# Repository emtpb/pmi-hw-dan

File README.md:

# PMI-DAN (Diodes And NMOS)

This pcb is designed for the course PMI (Practical course Microcontroller and Interface electronics). It features four LEDs and four open-drain NMOSFETs. It can be chained with [PMI-CARLOS](https://github.com/emtpb/pmi-hw-carlos) (thus only four of the available eight GPIO pins are used).

Pin header and sockets are compatible with
[Digilents Pmod](https://digilent.com/reference/pmod/start) interface.

The board can be used with [PMI-BOB2](https://github.com/emtpb/pmi-hw-bob2)
pcb.

# Interactive BOM

An interactive html BOM page with pcb layout and material placement can be found [here](https://emtpb.github.io/pmi-hw-dan/bom/ibom.html).

# Changelog

## 1.0
* First prototype

## 1.1
* First release

## 1.2
* Convert project to Kicad 6
* Round pcb corners
* Place output labeling above pin header

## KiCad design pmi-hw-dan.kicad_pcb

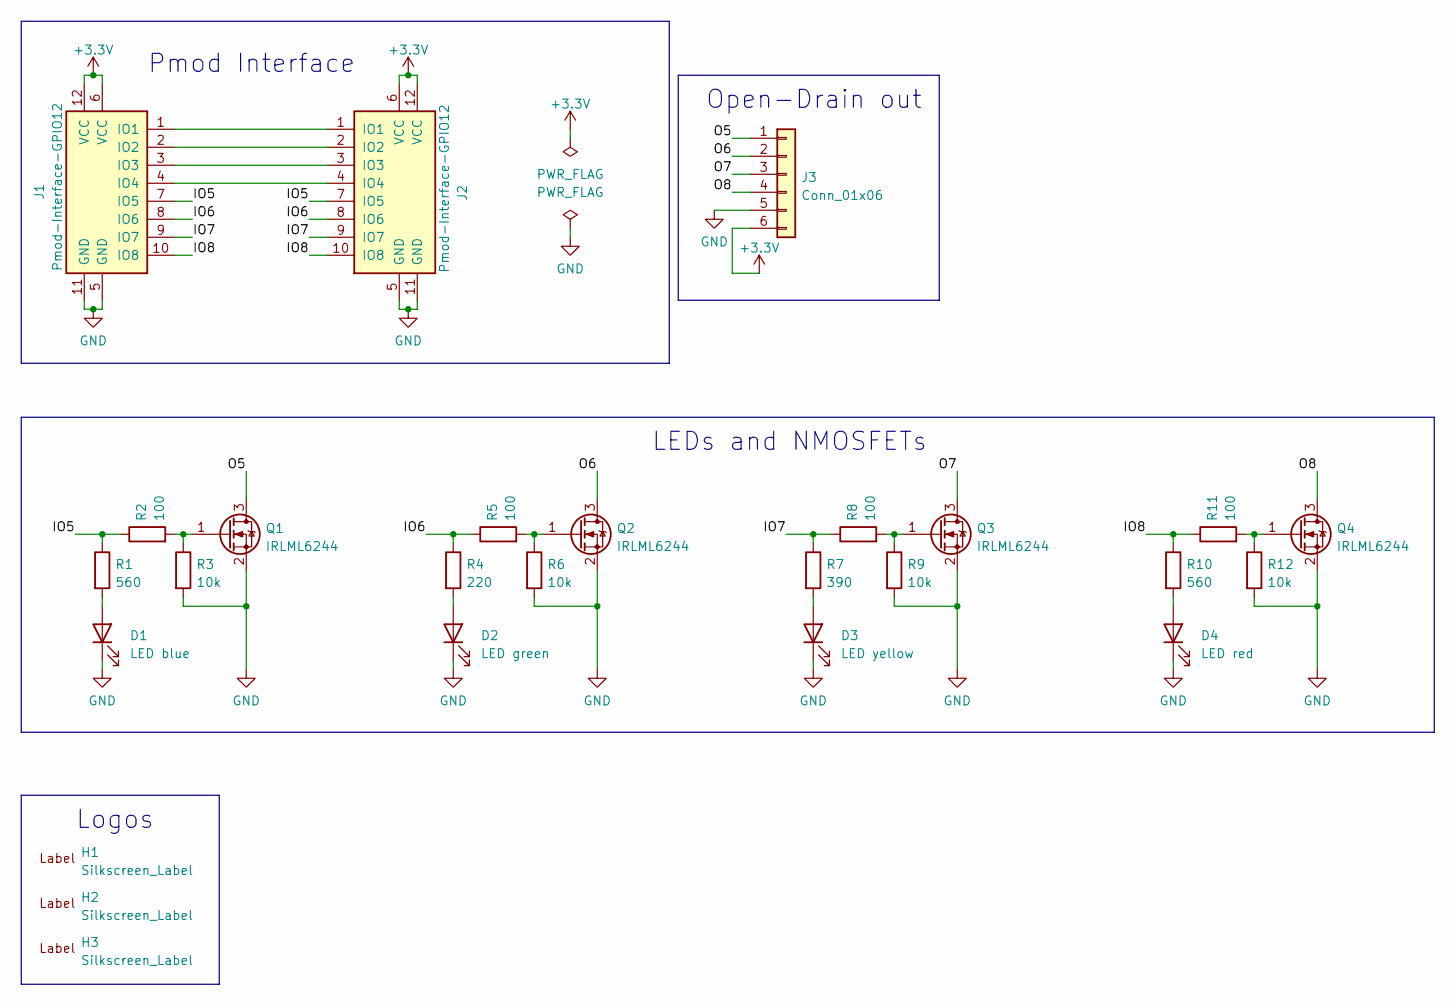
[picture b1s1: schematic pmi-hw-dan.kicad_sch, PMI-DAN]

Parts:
D1: LED blue; LED_0603_1608Metric; Manufacturer Part No LB Q39G-L2OO-35-1; Mouser Part No 720-LBQ39GL2N2351
D2: LED green; LED_0603_1608Metric; Manufacturer Part No LG Q396-PS-35; Digikey Part No 475-3754-1-ND
D3: LED yellow; LED_0603_1608Metric; Manufacturer Part No LY Q396-P1Q2-36; Digikey Part No 475-3467-1-ND
D4: LED red; LED_0603_1608Metric; Manufacturer Part No LS Q976-NR-1-0-20-R18; Digikey Part No 475-2512-1-ND
H1: Silkscreen_Label; UPB-Logo_En_12.3X4.3mm
H2, H3: Silkscreen_Label; EMT-Logo_8.2x4.1mm_Silkscreen
J1: Pmod-Interface-GPIO12; Pmod_Interface_Male12
J2: Pmod-Interface-GPIO12; Pmod_Interface_Female12
J3: Conn_01x06; PinHeader_1x06_P2.54mm_Vertical
Q1, Q2, Q3: IRLML6244; SOT-23
Q4: IRLML6244; SOT-23; Manufacturer Part No IRLML6244TRPBF; Digikey Part No IRLML6244TRPBFCT-ND
R1, R10: 560; R_0603_1608Metric
R2, R5, R8, R11: 100; R_0603_1608Metric
R3, R6, R9, R12: 10k; R_0603_1608Metric
R4: 220; R_0603_1608Metric
R7: 390; R_0603_1608Metric

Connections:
+3.3V: J1.6 (VCC), J1.12 (VCC), J2.6 (VCC), J2.12 (VCC), J3.6
/IO5: J1.7 (IO5), J2.7 (IO5), R1.1, R2.1
/IO6: J1.8 (IO6), J2.8 (IO6), R4.1, R5.1
/IO7: J1.9 (IO7), J2.9 (IO7), R7.1, R8.1
/IO8: J1.10 (IO8), J2.10 (IO8), R10.1, R11.1
/O5: J3.1, Q1.3 (D)
/O6: J3.2, Q2.3 (D)
/O7: J3.3, Q3.3 (D)
/O8: J3.4, Q4.3 (D)
GND: D1.1 (K), D2.1 (K), D3.1 (K), D4.1 (K), J1.5 (GND), J1.11 (GND), J2.5 (GND), J2.11 (GND), J3.5, Q1.2 (S), Q2.2 (S), Q3.2 (S), Q4.2 (S), R3.2, R6.2, R9.2, R12.2
unnamed: D1.2 (A), R1.2
unnamed: D2.2 (A), R4.2
unnamed: D3.2 (A), R7.2
unnamed: D4.2 (A), R10.2
unnamed: J1.1 (IO1), J2.1 (IO1)
unnamed: J1.2 (IO2), J2.2 (IO2)
unnamed: J1.3 (IO3), J2.3 (IO3)
unnamed: J1.4 (IO4), J2.4 (IO4)
unnamed: Q1.1 (G), R2.2, R3.1
unnamed: Q2.1 (G), R5.2, R6.1
unnamed: Q3.1 (G), R8.2, R9.1
unnamed: Q4.1 (G), R11.2, R12.1

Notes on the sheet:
Open-Drain out
Pmod Interface
LEDs and NMOSFETs
Logos

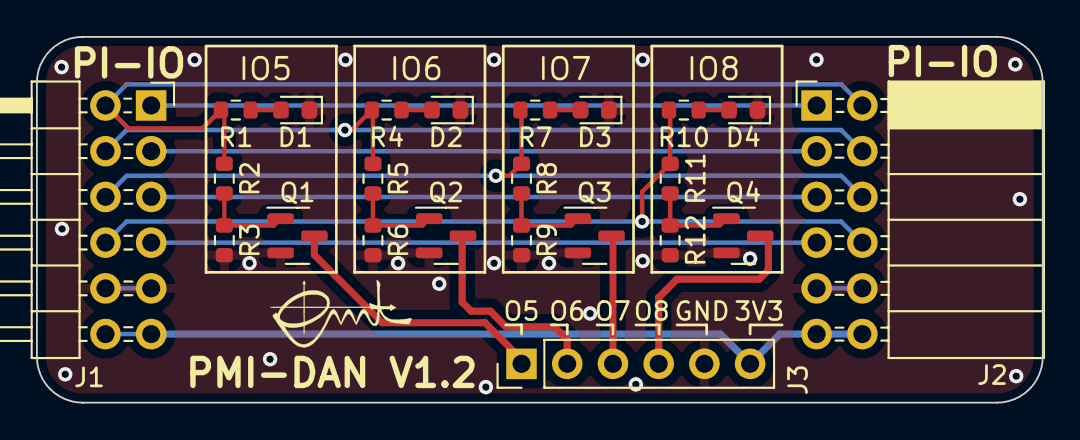
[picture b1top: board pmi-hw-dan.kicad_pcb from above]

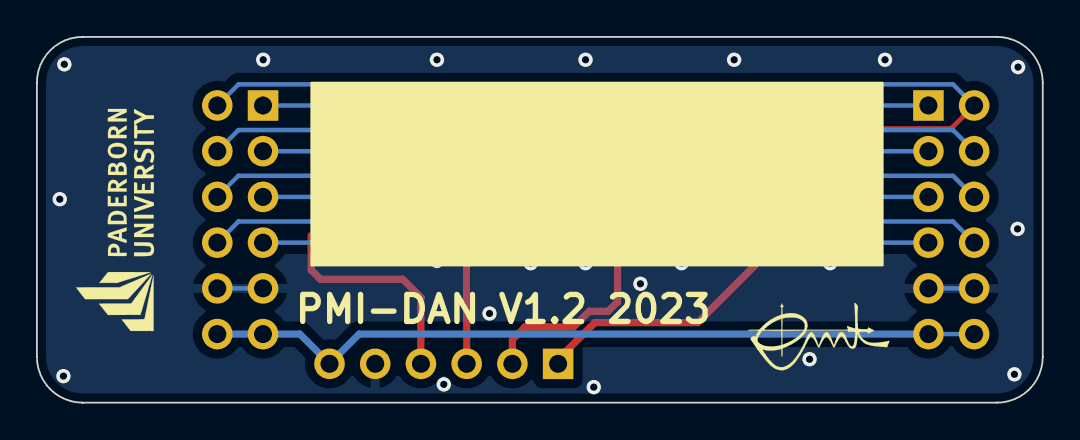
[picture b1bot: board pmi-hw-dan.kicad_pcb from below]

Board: 2 copper layers, 55.9 x 20.3 mm, 26 parts (2 on the bottom side), 22 nets.

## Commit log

2022-09-02 Add gitignore
2022-09-02 Add project files
2022-09-02 Add readme
2023-02-21 Bump to version 1.2
2025-05-22 Add interactive BOM link
